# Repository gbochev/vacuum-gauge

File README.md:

# Vacuum gauge
Simple Arduino-based vacuum gauge for Pirani and Thermocouple sensor types

### Description
While developing a vacuum system used for homemade PVD sputtering aparatus I felt the need of a simple and cheap vacuum gauge that can measure pressures as low as 1 Pa. I was not able to find online a finished DIY project thus I created one. The main idea is to use a standard thermocouple sensor at first (some of them are expensive) and then try to transition to a simple Pirani type sensor which can even be a small lightbulb (the lightbulbs are commonly available and probably have relatively the same resistance and performance so once calibrated one can have very cheap sensor).

This project is still work in progress. Next steps will be to connect a thermocouple that has a datasheet (specifying the pressure in Pa and the mV output) interpolate the points from the datasheet and then place it into the arduino code. After that experiments with commonly available light bulbs can begin.
Since the lightbulbs (and some thermocouple gauges) need to operate under vacuum, two relays are added to stop the supply when the system is not under vacuum. 

### Tips
As some chinese Arduino clones do not have connected (or have them wrongly connected) protection diodes please be careful (or best advice - do not supply the board by the external supply and the USB at the same time) when you supply the board externally.

Mount all transistors and regulators on heatsinks as they will heat up during measurement.

Some cheap thermocouple gauges that I found are called: ЛТ-2 (LT-2) and ЛТ-4М (LT-4M). They can sometimes be found on ebay for a good price.

### Schematic
[You can view it here](vacuum_gauge.pdf)
### PCB
PCB is located in the pcb folder. It is created with KiCAD. You can order the PCB directly by using the production.zip (file that contains the exported gerber files).

### Arduino code
The Arduino code is located in the arduino-code folder. The code still lacks the ability to measure pressure and it is a mess (I merged several online projects). It measures the pressure in mV. As next steps conversion tables for different sensor types will be added. In order to use it, please install the libraries (Adafruit and the others) that are referenced on the top of the file.

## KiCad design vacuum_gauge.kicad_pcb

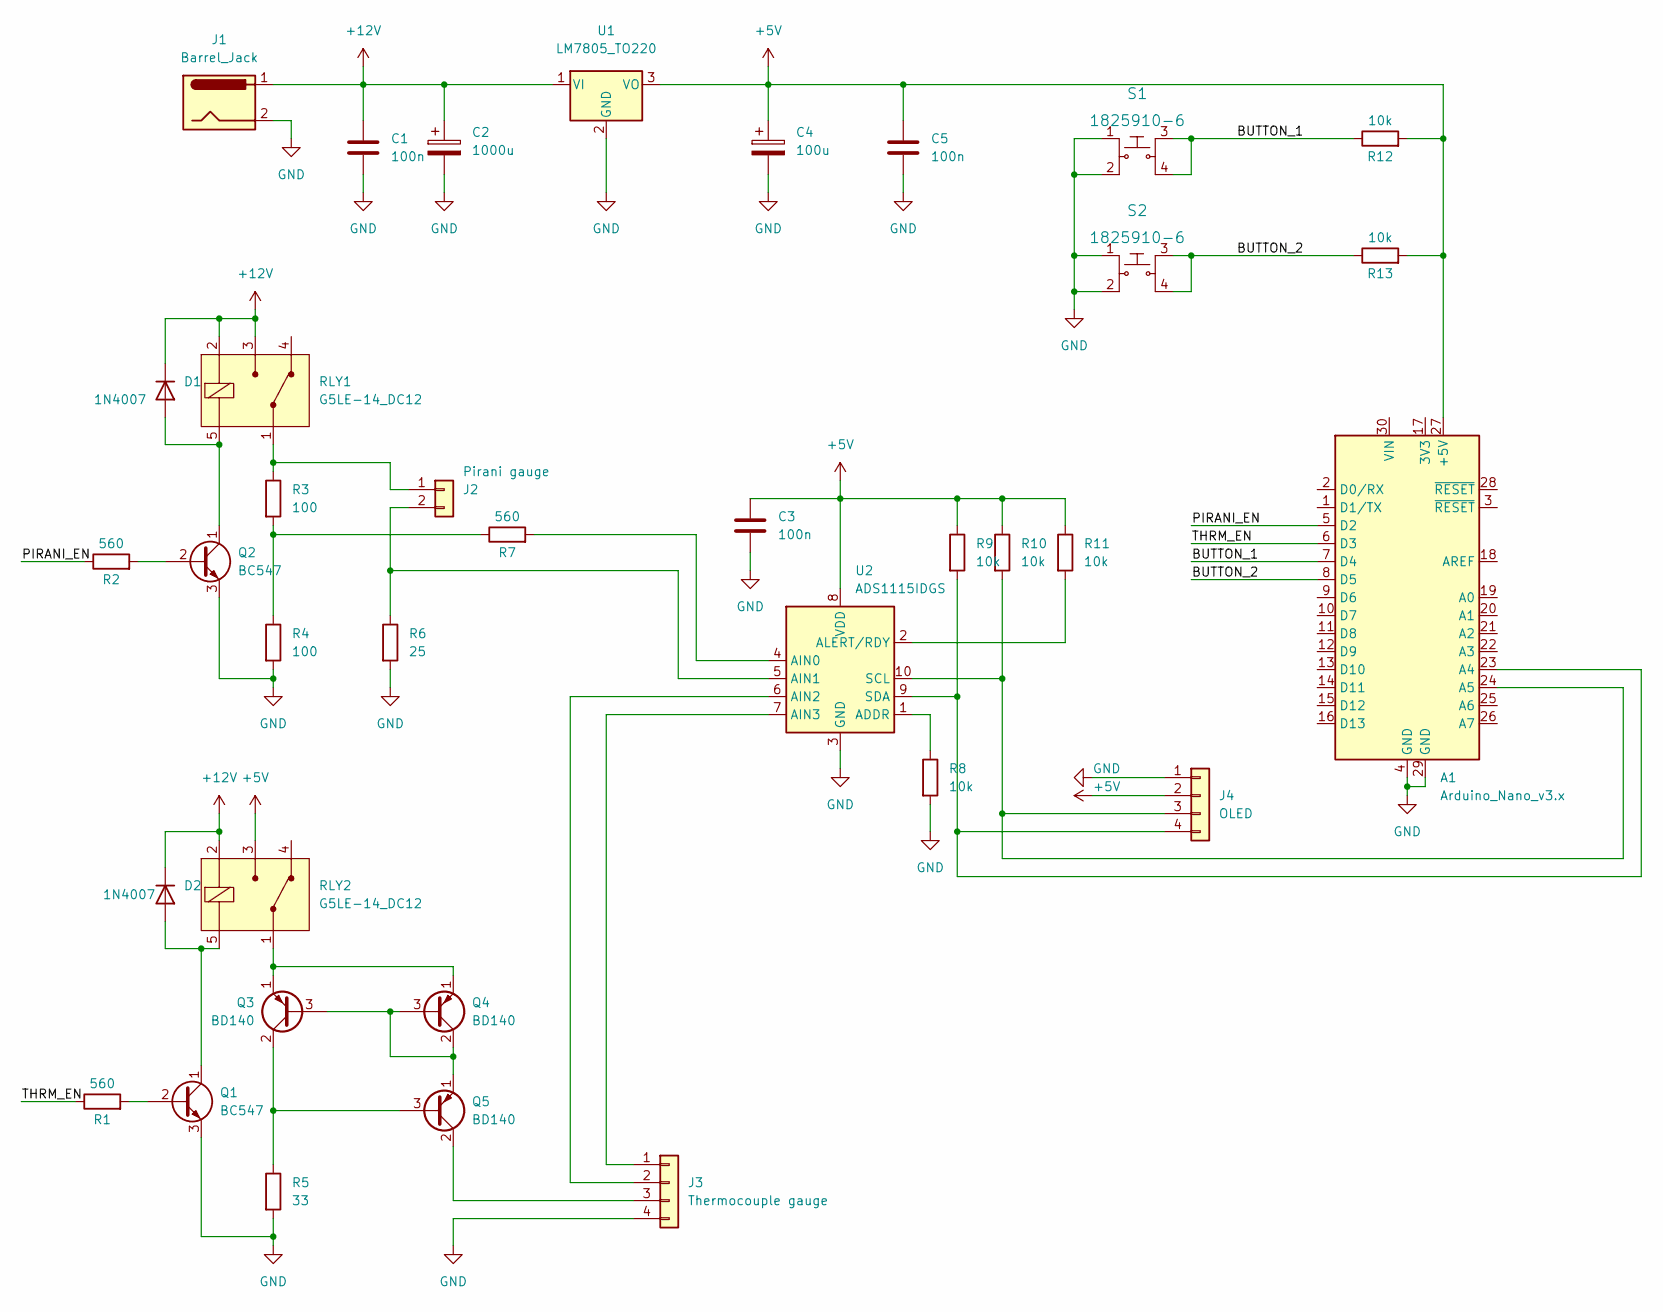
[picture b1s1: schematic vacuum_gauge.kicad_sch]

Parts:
A1: Arduino_Nano_v3.x; Arduino_Nano
C1, C3, C5: 100n; C_Rect_L10.0mm_W4.0mm_P7.50mm_MKS4
C2: 1000u; CP_Radial_D14.0mm_P7.50mm
C4: 100u; CP_Radial_D14.0mm_P7.50mm
D1, D2: 1N4007; D_DO-41_SOD81_P10.16mm_Horizontal
J1: Barrel_Jack; BarrelJack_GCT_DCJ200-10-A_Horizontal
J2: Pirani gauge; PinHeader_1x02_P2.54mm_Vertical
J3: Thermocouple gauge; PinHeader_1x04_P2.54mm_Vertical
J4: OLED; PinHeader_1x04_P2.54mm_Vertical
Q1, Q2: BC547; TO-92_Inline
Q3, Q4, Q5: BD140; TO-126-3_Vertical
R1, R2, R7: 560; R_Axial_DIN0309_L9.0mm_D3.2mm_P15.24mm_Horizontal
R3, R4: 100; R_Axial_DIN0309_L9.0mm_D3.2mm_P15.24mm_Horizontal
R5: 33; R_Axial_DIN0309_L9.0mm_D3.2mm_P15.24mm_Horizontal
R6: 25; R_Axial_DIN0309_L9.0mm_D3.2mm_P15.24mm_Horizontal
R8, R9, R10, R11, R12, R13: 10k; R_Axial_DIN0309_L9.0mm_D3.2mm_P15.24mm_Horizontal
RLY1, RLY2: G5LE-14_DC12; Relay_THT_G5LE-14; MPN G5LE-14 DC12; Digi-Key_PN Z1012-ND
S1, S2: 1825910-6; Switch_Tactile_THT_6x6mm; MPN 1825910-6; Digi-Key_PN 450-1650-ND
U1: LM7805_TO220; TO-220-3_Vertical
U2: ADS1115IDGS; TSSOP-10_3x3mm_P0.5mm

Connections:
+5V: A1.27 (+5V), C3.1, C4.1, C5.1, J4.2, R9.1, R10.1, R11.1, R12.2, R13.2, RLY2.3 (NO), U1.3 (VO), U2.8 (VDD)
+12V: C1.1, C2.1, D1.1 (K), D2.1 (K), J1.1, RLY1.2 (COIL), RLY1.3 (NO), RLY2.2 (COIL), U1.1 (VI)
/BUTTON_1: A1.7 (D4), R12.1, S1.3, S1.4
/BUTTON_2: A1.8 (D5), R13.1, S2.3, S2.4
/PIRANI_EN: A1.5 (D2), R2.1
/THRM_EN: A1.6 (D3), R1.1
GND: A1.4 (GND), A1.29 (GND), C1.2, C2.2, C3.2, C4.2, C5.2, J1.2, J3.4, J4.1, Q1.3 (E), Q2.3 (E), R4.2, R5.2, R6.2, R8.2, S1.1, S1.2, S2.1, S2.2, U1.2 (GND), U2.3 (GND)
unnamed: A1.23 (A4), J4.4, R9.2, U2.9 (SDA)
unnamed: A1.24 (A5), J4.3, R10.2, U2.10 (SCL)
unnamed: D1.2 (A), Q2.1 (C), RLY1.5 (COIL)
unnamed: D2.2 (A), Q1.1 (C), RLY2.5 (COIL)
unnamed: J2.1, R3.1, RLY1.1 (COM)
unnamed: J2.2, R6.1, U2.5 (AIN1)
unnamed: J3.1, U2.7 (AIN3)
unnamed: J3.2, U2.6 (AIN2)
unnamed: J3.3, Q5.2 (C)
unnamed: Q1.2 (B), R1.2
unnamed: Q2.2 (B), R2.2
unnamed: Q3.1 (E), Q4.1 (E), RLY2.1 (COM)
unnamed: Q3.2 (C), Q5.3 (B), R5.1
unnamed: Q3.3 (B), Q4.2 (C), Q4.3 (B), Q5.1 (E)
unnamed: R3.2, R4.1, R7.1
unnamed: R7.2, U2.4 (AIN0)
unnamed: R8.1, U2.1 (ADDR)
unnamed: R11.2, U2.2 (ALERT/RDY)

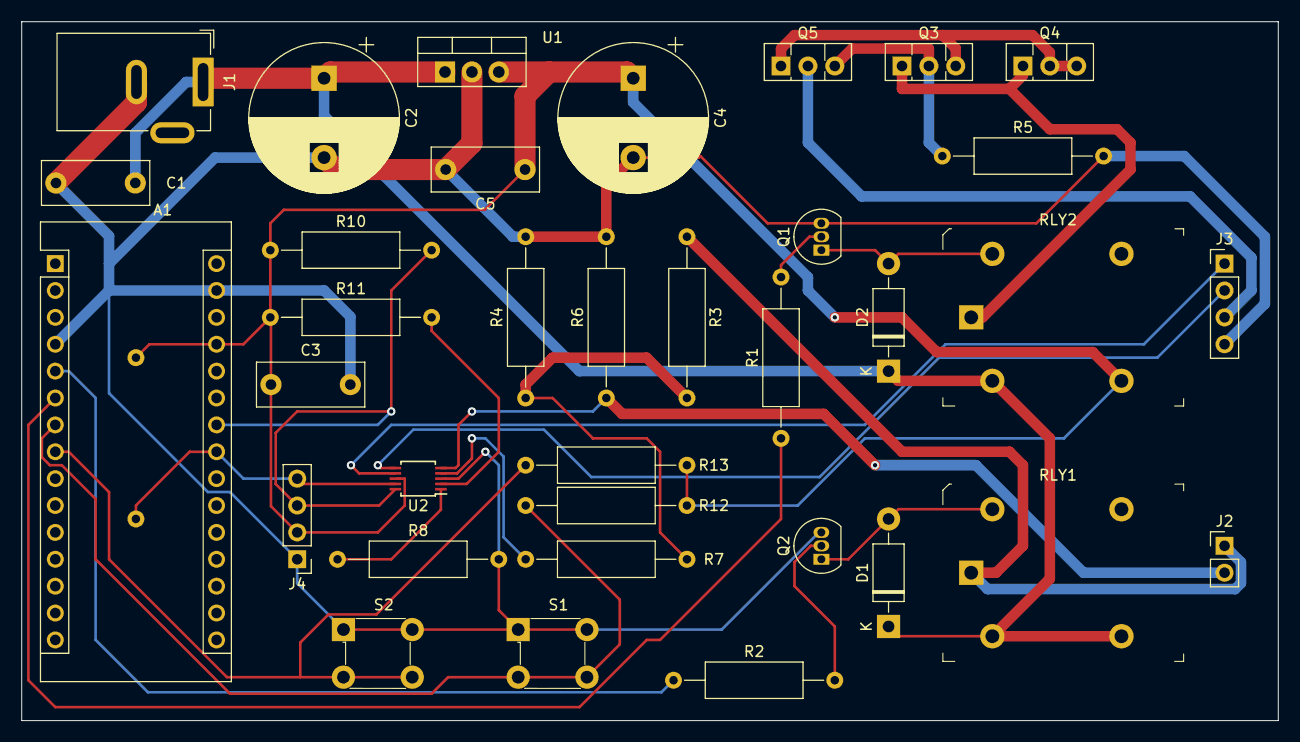
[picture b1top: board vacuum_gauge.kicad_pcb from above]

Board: 2 copper layers, 118.7 x 66.0 mm, 36 parts (1 on the bottom side), 25 nets.

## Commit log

2025-05-31 Add files via upload
    Initial commit
2025-05-31 Rename vacuum_gauge.kicad_prl to pcb/vacuum_gauge.kicad_prl
2025-05-31 Rename vacuum_gauge.kicad_pro to pcb/vacuum_gauge.kicad_pro
